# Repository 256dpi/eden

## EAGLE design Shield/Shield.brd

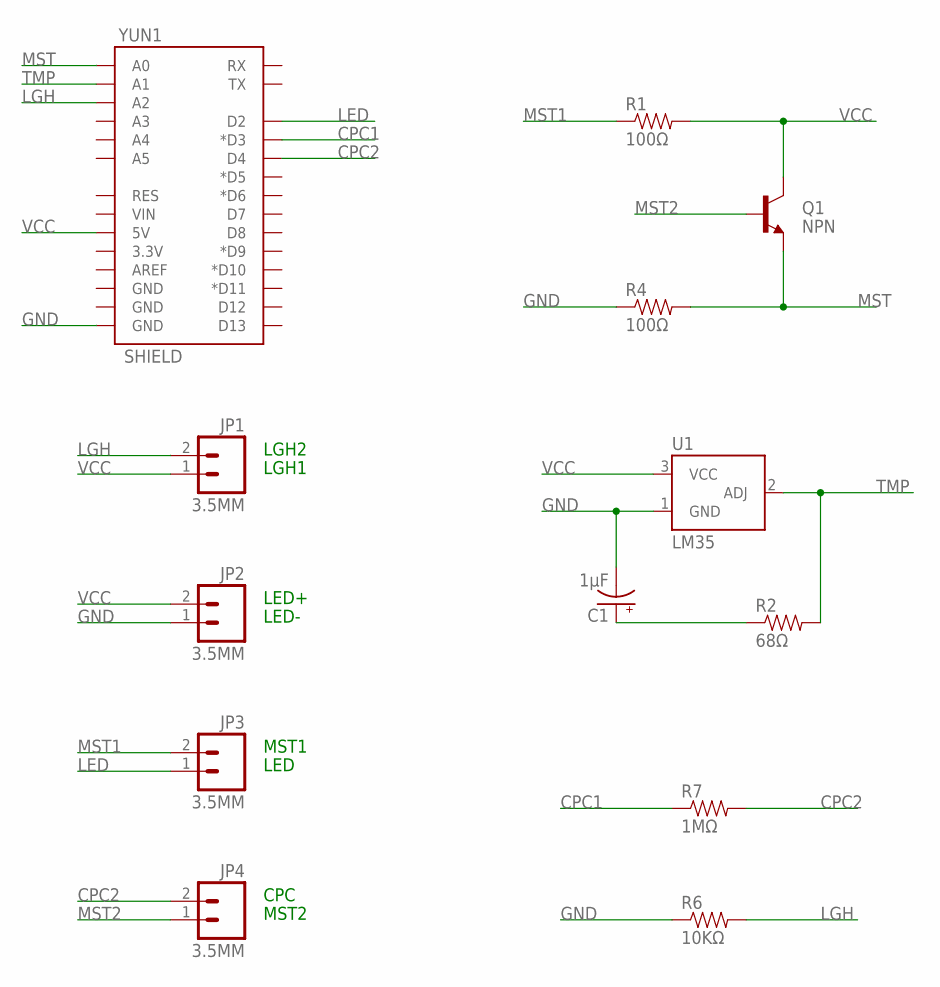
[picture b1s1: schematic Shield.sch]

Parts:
C1: 1µF; CPOL-RADIAL-100UF-25V
JP1, JP2, JP3, JP4: 3.5MM; SCREWTERMINAL-3.5MM-2
Q1: NPN; TO-92-AMMO
R1, R4: 100Ω; AXIAL-0.3
R2: 68Ω; AXIAL-0.3
R6: 10KΩ; AXIAL-0.3
R7: 1MΩ; AXIAL-0.3
U1: LM35; TO-92
YUN1: SHIELD; DUEMILANOVE_VIAS

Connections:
CPC1: R7.P$1 (1), YUN1.D3 (*D3)
CPC2: JP4.2, R7.P$2 (2), YUN1.D4
GND: C1.2 (-), JP2.1, R4.P$1 (1), R6.P$1 (1), U1.1 (GND), YUN1.GND@0 (GND)
LED: JP3.1, YUN1.D2
LGH: JP1.2, R6.P$2 (2), YUN1.A2
MST: Q1.3 (E), R4.P$2 (2), YUN1.A0
MST1: JP3.2, R1.P$1 (1)
MST2: JP4.1, Q1.2 (B)
unnamed: C1.1 (+), R2.P$1 (1)
TMP: R2.P$2 (2), U1.2 (ADJ), YUN1.A1
VCC: JP1.1, JP2.2, Q1.1 (C), R1.P$2 (2), U1.3 (VCC), YUN1.5V

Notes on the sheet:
LGH2
LGH1
LED+
LED-
LED
MST1
CPC
MST2

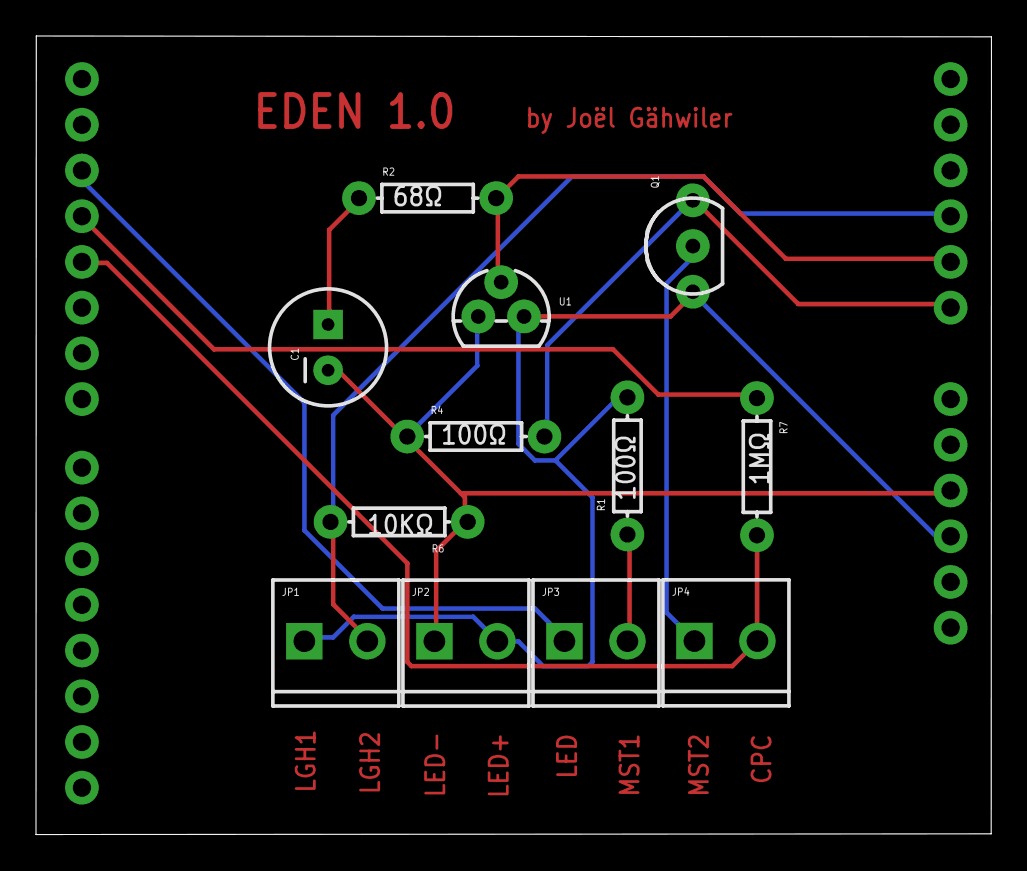
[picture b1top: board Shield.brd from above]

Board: 2 copper layers, 53.1 x 44.4 mm, 13 parts (0 on the bottom side), 11 nets.

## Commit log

2015-02-09 added first sensor
2015-02-11 set LED high if connected
2015-02-11 added number datatype
2015-02-11 added simple display
2015-02-11 renamed to controller
2015-02-11 changed name
2015-02-11 work in progress ring animation
2015-02-11 better with precision
2015-02-11 send ring numbers
2015-02-11 finished animation
2015-02-12 consolidated files
2015-02-12 change doc
2015-02-12 added touch sensor
2015-02-13 simplified
2015-02-13 added temperature
2015-02-13 added light sensor
2015-02-13 added temperature smoothing
2015-02-13 send percentages
2015-02-13 make sure LEDs are off on triple zero
2015-02-13 style
2015-02-13 fixed server
2015-02-13 use concrete values
2015-02-13 added color animations
2015-02-13 show animation
2015-02-16 added alarm stuff
2015-02-16 added state module
2015-02-17 support multiple pots
2015-02-17 added alarm forward
2015-02-18 only check bit zero
2015-02-18 renamed some things
2015-02-18 added support for short and long touches
2015-02-18 long touch wakes all pots
2015-02-18 many optimizations
2015-02-18 added moisture alarm
2015-02-18 removed loop
2015-02-18 magenta rather than yellow
2015-02-19 use pin 2
2015-02-19 using a more simple approach for touch sensing
2015-02-19 started with a shield
2015-02-19 fixed D2 pin
2015-02-20 finished shield v1.0
2015-02-20 print with copper
2015-02-20 optimized wiring
2015-02-20 set window position
2015-02-20 smooth value with capacitor
2015-02-20 added capacitor to temperature circuit
2015-02-20 better fonts
2015-02-20 distribute analog readings
2015-02-20 just a monitor
2015-02-20 a completely autonomous setup
2015-02-23 callibrated moisture
2015-02-26 added temperature display
2015-02-26 added first pot design with rhino
2015-02-27 use modules to work with PyCharm
2015-02-27 finished a simple pot
2015-02-27 line feed
2015-02-27 generate pot using revolve function
2015-02-27 added simple rounded top edge
2015-02-27 added ring emboss on inner side
2015-02-27 measure inner pot values
2015-02-27 parametrized generation
2015-02-27 fix bug
2015-02-27 added arduino cut out
2015-04-02 changed pins to match shield layout
2015-04-07 minor updates
2015-04-09 switched to more efficient client library
2015-04-09 added channel selection
2015-04-10 removed channel stuff
2015-04-14 updated pot design

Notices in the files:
parts and their libraries:
SparkFun-Boards: Licensing: Creative Commons ShareAlike 4.0 International - https://creativecommons.org/licenses/by-sa/4.0
